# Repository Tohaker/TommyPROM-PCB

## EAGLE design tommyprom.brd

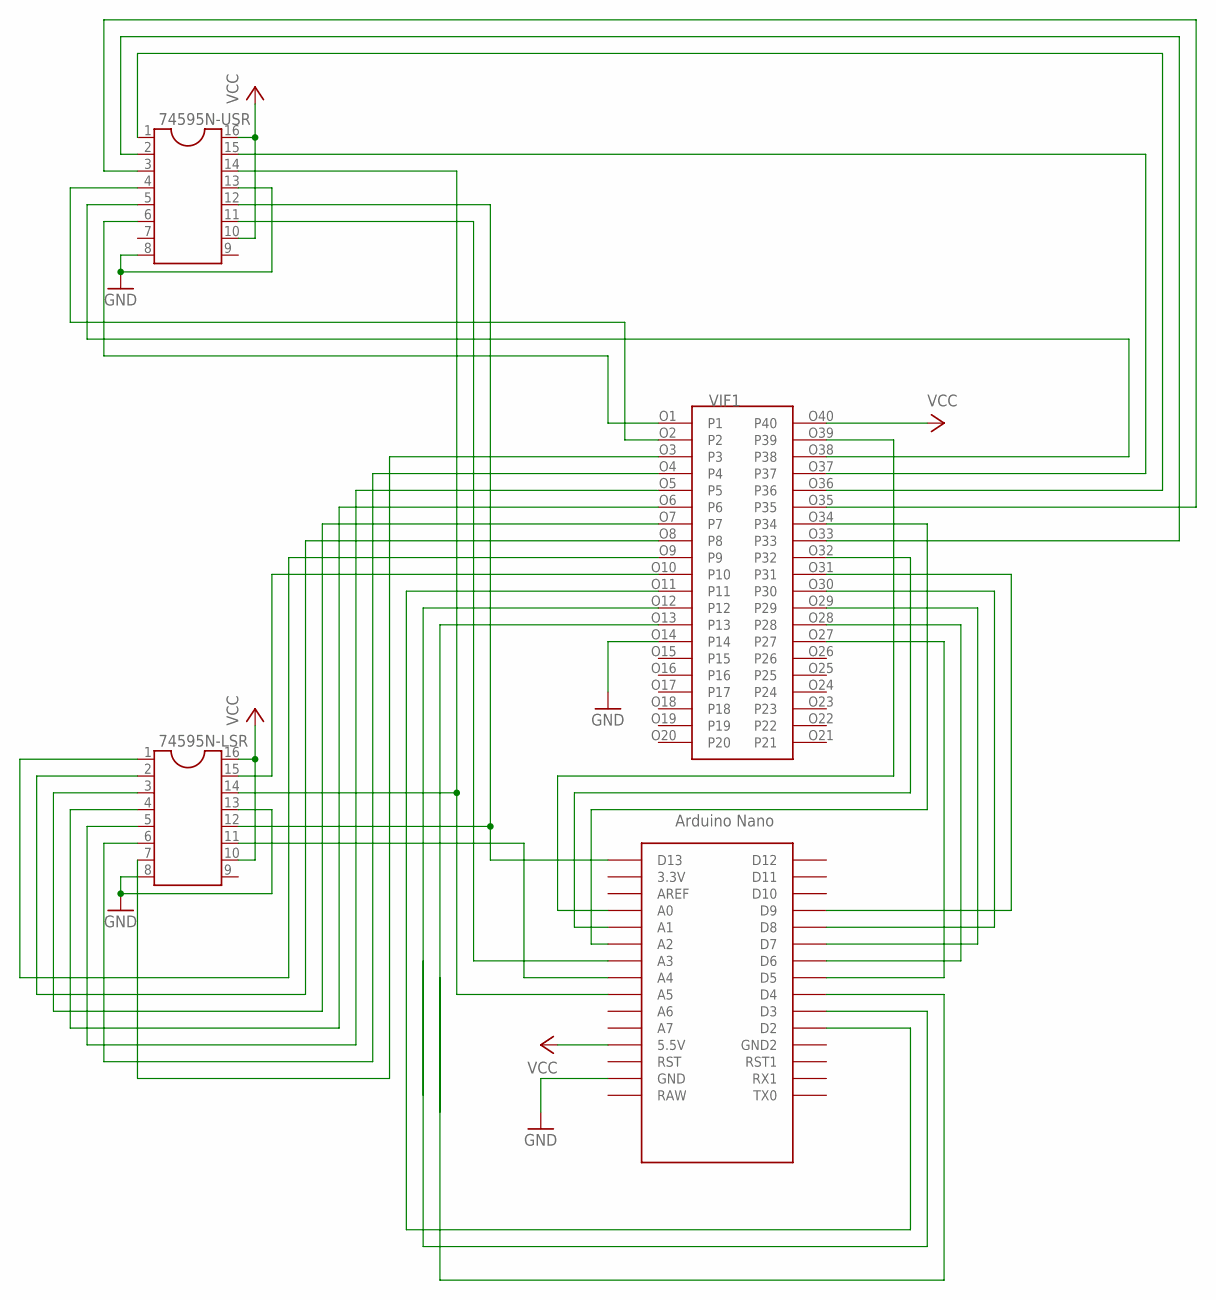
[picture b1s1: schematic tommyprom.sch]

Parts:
74595N-LSR, 74595N-USR: DIL16S; SOCKET-16
U$1: NANO
VIF1: 40-6554-10DIP; 40-6554-10

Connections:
GND: 74595N-LSR.8, 74595N-LSR.13, 74595N-USR.8, 74595N-USR.13, U$1.GND, VIF1.O14 (P14)
unnamed: 74595N-USR.15, VIF1.O37 (P37)
unnamed: 74595N-USR.5, VIF1.O38 (P38)
unnamed: 74595N-LSR.12, 74595N-USR.12, U$1.D13
unnamed: 74595N-USR.3, VIF1.O35 (P35)
unnamed: 74595N-USR.11, U$1.A3
unnamed: 74595N-LSR.14, 74595N-USR.14, U$1.A5
unnamed: 74595N-USR.6, VIF1.O1 (P1)
unnamed: 74595N-USR.1, VIF1.O36 (P36)
unnamed: 74595N-LSR.15, VIF1.O10 (P10)
unnamed: 74595N-LSR.1, VIF1.O9 (P9)
unnamed: 74595N-LSR.2, VIF1.O8 (P8)
unnamed: 74595N-LSR.3, VIF1.O7 (P7)
unnamed: 74595N-LSR.4, VIF1.O6 (P6)
unnamed: 74595N-LSR.5, VIF1.O5 (P5)
unnamed: 74595N-LSR.6, VIF1.O4 (P4)
unnamed: 74595N-LSR.7, VIF1.O3 (P3)
unnamed: U$1.A0, VIF1.O39 (P39)
unnamed: U$1.A1, VIF1.O32 (P32)
unnamed: U$1.A2, VIF1.O34 (P34)
unnamed: 74595N-LSR.11, U$1.A4
unnamed: 74595N-USR.2, VIF1.O33 (P33)
unnamed: 74595N-USR.4, VIF1.O2 (P2)
unnamed: U$1.D2, VIF1.O11 (P11)
unnamed: U$1.D3, VIF1.O12 (P12)
unnamed: U$1.D4, VIF1.O13 (P13)
unnamed: U$1.D5, VIF1.O27 (P27)
unnamed: U$1.D6, VIF1.O28 (P28)
unnamed: U$1.D7, VIF1.O29 (P29)
unnamed: U$1.D8, VIF1.O30 (P30)
unnamed: U$1.D9, VIF1.O31 (P31)
VCC: 74595N-LSR.10, 74595N-LSR.16, 74595N-USR.10, 74595N-USR.16, U$1.5V (5.5V), VIF1.O40 (P40)

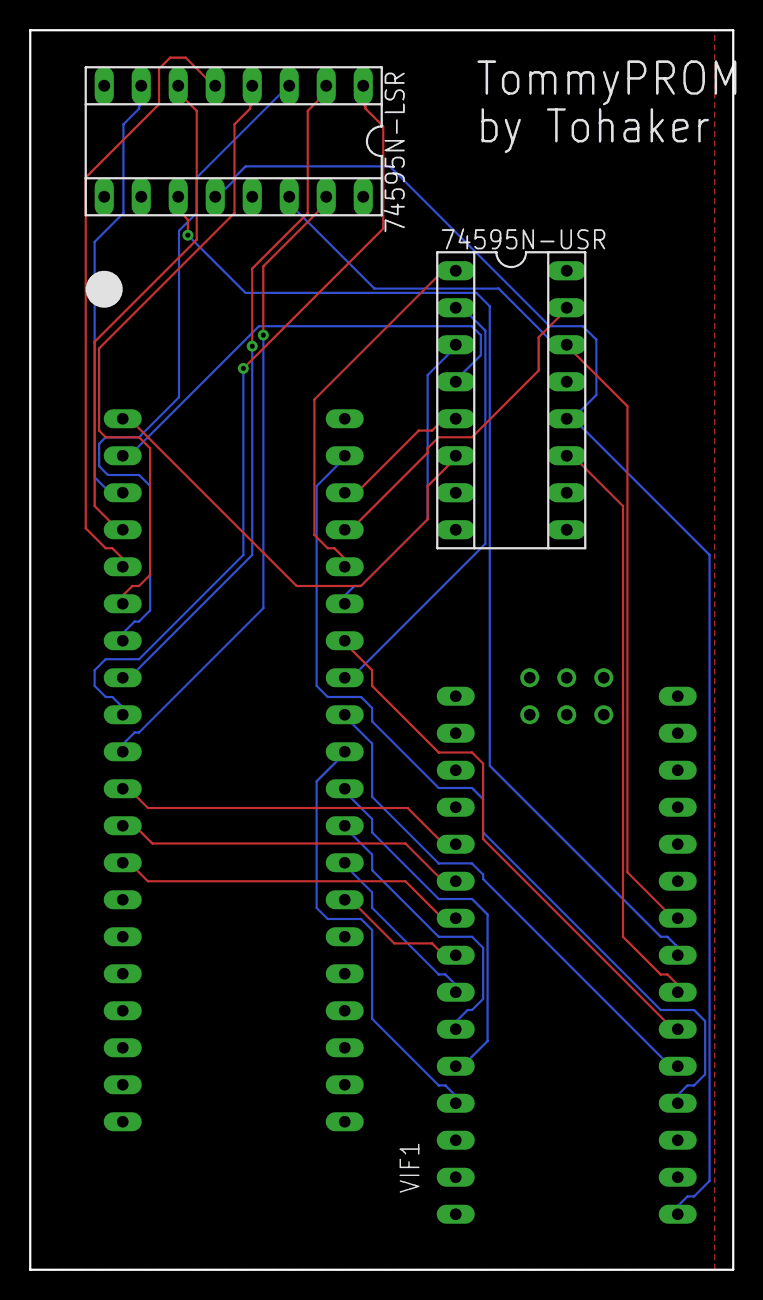
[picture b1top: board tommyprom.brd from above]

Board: 2 copper layers, 48.3 x 85.1 mm, 4 parts (0 on the bottom side), 32 nets.
